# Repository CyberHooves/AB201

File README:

Haos Redro
==========

README for AB201
----------------

The AB201 is a class-AB audio amplifier module designed to have a sufficiently low profile to fit into 1U rack-mounting cases. It has been designed to provide up to 200W RMS output power before clipping. Output powers of up to 300W may be possible with sufficient cooling but is NOT reccommended with the specified heatsink (Fischer Electronic SK499 profile)

Notes on cooling:
-----------------
This module requires forced air cooling. The enclosure into which this module is installed must be designed to move air through the heatsink. There is provision for a two-lead temperature sensor for fan control and a TO-220 packaged NC thermostat to disconnect the output in case of overheating.

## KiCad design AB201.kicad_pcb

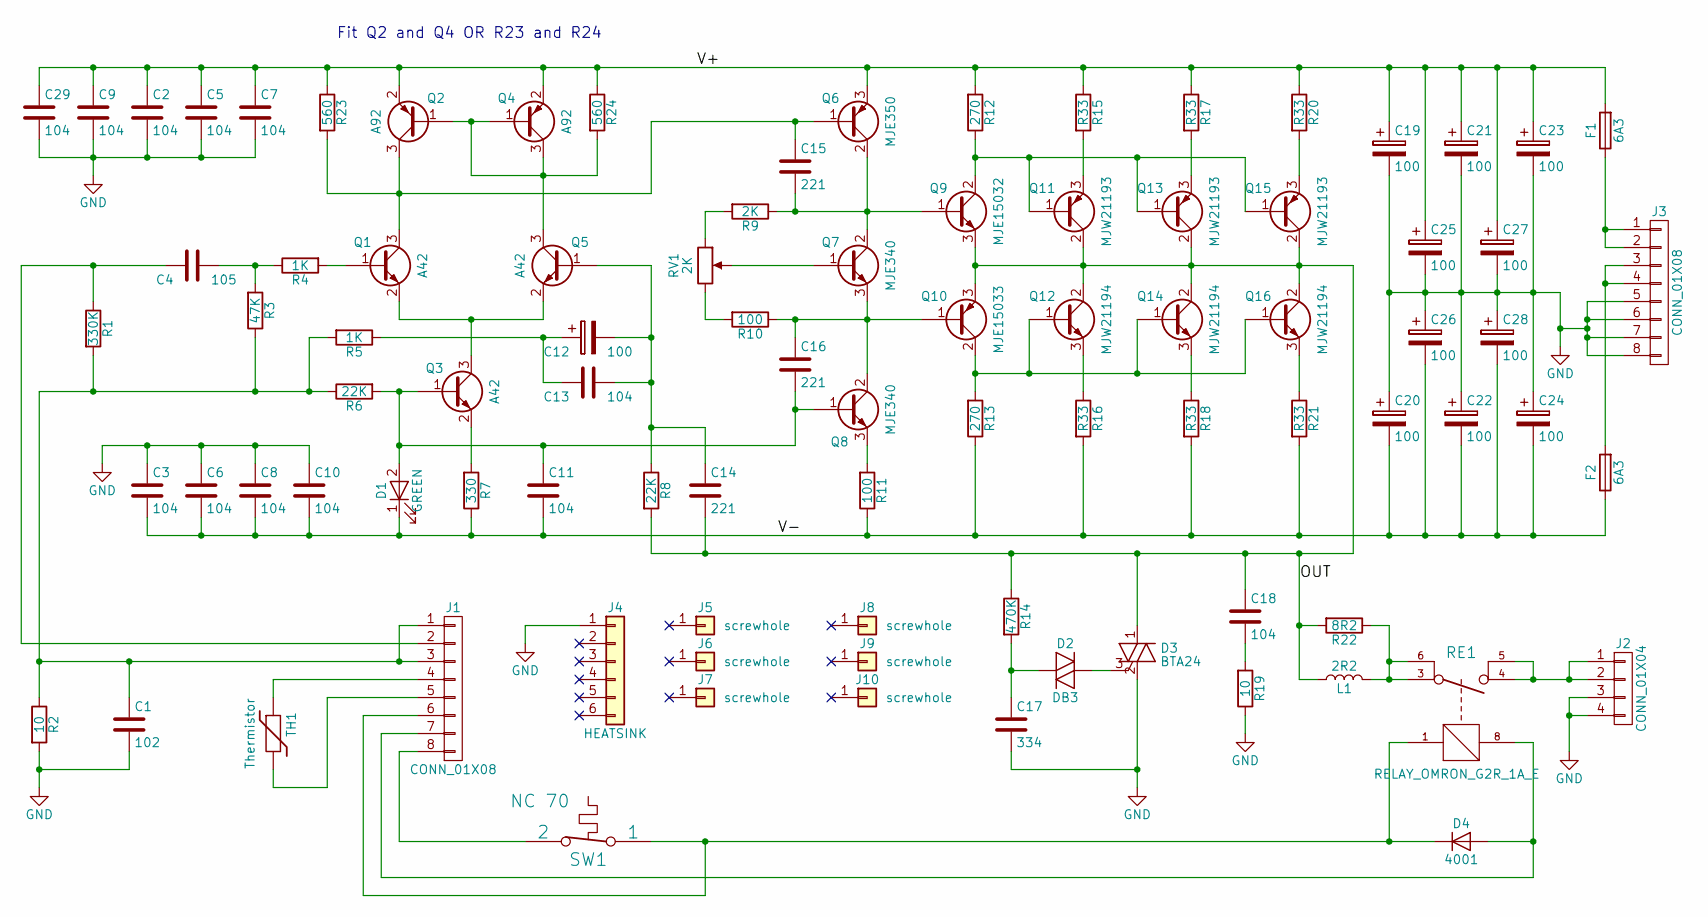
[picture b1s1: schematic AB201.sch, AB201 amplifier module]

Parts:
C1: 102; C_0805
C2, C3, C5, C6, C7, C8, C9, C10, C11, C29: 104; C_0805
C4: 105; C_Rect_L7.2mm_W5.5mm_P5.00mm_FKS2_FKP2_MKS2_MKP2
C12: 100; CP_Radial_D6.3mm_P2.50mm
C13: 104; C_Rect_L7.2mm_W3.0mm_P5.00mm_FKS2_FKP2_MKS2_MKP2
C14, C15, C16: 221; C_0805
C17: 334; C_0805
C18: 104; C_Rect_L7.2mm_W5.5mm_P5.00mm_FKS2_FKP2_MKS2_MKP2
C19, C20, C21, C22, C23, C24, C25, C26, C27, C28: 100; CP_Radial_D10.0mm_P5.00mm
D1: GREEN; LED_0805
D2: DB3; D_MiniMELF
D3: BTA24; TO-220-3_Vertical
D4: 4001; D_SMA
F1, F2: 6A3; Fuseholder5x20_horiz_open_universal_Type-III
J1: CONN_01X08; Pin_Header_Straight_2x04_Pitch2.54mm
J2: CONN_01X04; Molex_MiniFit-JR-5556-04A_2x02x4.20mm_Straight
J3: CONN_01X08; Molex_MiniFit-JR-5556-08A_2x04x4.20mm_Straight
J4: HEATSINK; HS-FISCHER-SK499-200-6A
J5, J6, J7, J8, J9, J10: screwhole; MH-H3.2-P7
L1: 2R2; Choke_SMD_10.4x10.4_H4.8
Q1, Q3, Q5: A42; SOT-23
Q2, Q4: A92; SOT-23
Q6: MJE350; TO-126_Vertical
Q7, Q8: MJE340; TO-126_Vertical
Q9: MJE15032; TO-220-3_Vertical
Q10: MJE15033; TO-220-3_Vertical
Q11, Q13, Q15: MJW21193; TO-247_TO-3P_Vertical
Q12, Q14, Q16: MJW21194; TO-247_TO-3P_Vertical
R1: 330K; R_0805
R2: 10; R_0805
R3: 47K; R_0805
R4, R5: 1K; R_0805
R6, R8: 22K; R_0805
R7: 330; R_0805
R9: 2K; R_0805
R10, R11: 100; R_0805
R12, R13: 270; R_1218
R14: 470K; R_0805
R15, R16, R17, R18, R20, R21: R33; R_Radial_Power_L13.0mm_W9.0mm_P5.00mm
R19: 10; R_Axial_DIN0922_L20.0mm_D9.0mm_P7.62mm_Vertical
R22: 8R2; R_Axial_Power_L20.0mm_W6.4mm_P7.62mm_Vertical
R23, R24: 560; R_0805
RE1: RELAY_OMRON_G2R_1A_E; RELAY-OMRON-G2R-1A-E
RV1: 2K; Potentiometer_Trimmer_Bourns_3296W
SW1: NC 70; TO-220-2_Vertical
TH1: Thermistor; PINHEAD1-2

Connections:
/OUT: C14.2, C18.1, D3.1 (A1), L1.1, Q9.3 (E), Q10.3 (E), Q11.2 (C), Q12.2 (C), Q13.2 (C), Q14.2 (C), Q15.2 (C), Q16.2 (C), R8.2, R14.1, R22.2
/V+: C2.1, C5.1, C7.1, C9.1, C19.1, C21.1, C23.1, C25.1, C27.1, C29.1, F1.2, Q2.2 (E), Q4.2 (E), Q6.3 (E), R12.2, R15.1, R17.1, R20.1, R23.1, R24.1
/V-: C3.2, C6.2, C8.2, C10.2, C11.2, C20.2, C22.2, C24.2, C26.2, C28.2, D1.1 (K), F2.1, R7.1, R11.1, R13.1, R16.2, R18.2, R21.2
GND: C1.2, C2.2, C3.1, C5.2, C6.1, C7.2, C8.1, C9.2, C10.1, C17.2, C19.2, C20.1, C21.2, C22.1, C23.2, C24.1, C25.2, C26.1, C27.2, C28.1, C29.2, D3.2 (A2), J2.3, J2.4, J3.5, J3.6, J3.7, J3.8, J4.1, R2.2, R19.1
unnamed: C1.1, J1.1, J1.3, R1.2, R2.1, R3.1, R5.2, R6.1
unnamed: C4.1, J1.2, R1.1
unnamed: C4.2, R3.2, R4.1
unnamed: C11.1, C16.2, D1.2 (A), Q3.1 (B), Q8.1 (B), R6.2
unnamed: C12.1, C13.1, R5.1
unnamed: C12.2, C13.2, C14.1, Q5.1 (B), R8.1
unnamed: C15.1, Q1.3 (C), Q2.3 (C), Q6.1 (B), R23.2
unnamed: C15.2, Q6.2 (C), Q7.2 (C), Q9.1 (B), R9.1
unnamed: C16.1, Q7.3 (E), Q8.2 (C), Q10.1 (B), R10.1
unnamed: C17.1, D2.1 (K), R14.2
unnamed: C18.2, R19.2
unnamed: D2.2 (A), D3.3 (G)
unnamed: D4.1 (K), J1.6, RE1.1 (C1), SW1.1
unnamed: D4.2 (A), J1.7, RE1.8 (C2)
unnamed: F1.1, J3.1, J3.2
unnamed: F2.2, J3.3, J3.4
unnamed: J1.4, TH1.1
unnamed: J1.5, TH1.2
unnamed: J1.8, SW1.2
unnamed: J2.1, J2.2, RE1.4, RE1.5
unnamed: L1.2, R22.1, RE1.3, RE1.6
unnamed: Q1.1 (B), R4.2
unnamed: Q1.2 (E), Q3.3 (C), Q5.2 (E)
unnamed: Q2.1 (B), Q4.1 (B), Q4.3 (C), Q5.3 (C), R24.2
unnamed: Q3.2 (E), R7.2
unnamed: Q7.1 (B), RV1.2
unnamed: Q8.3 (E), R11.2
unnamed: Q10.2 (C), Q12.1 (B), Q14.1 (B), Q16.1 (B), R13.2
unnamed: Q9.2 (C), Q11.1 (B), Q13.1 (B), Q15.1 (B), R12.1
unnamed: Q11.3 (E), R15.2
unnamed: Q12.3 (E), R16.1
unnamed: Q13.3 (E), R17.2
unnamed: Q14.3 (E), R18.1
unnamed: Q15.3 (E), R20.2
unnamed: Q16.3 (E), R21.1
unnamed: R9.2, RV1.1
unnamed: R10.2, RV1.3

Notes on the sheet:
Fit Q2 and Q4 OR R23 and R24

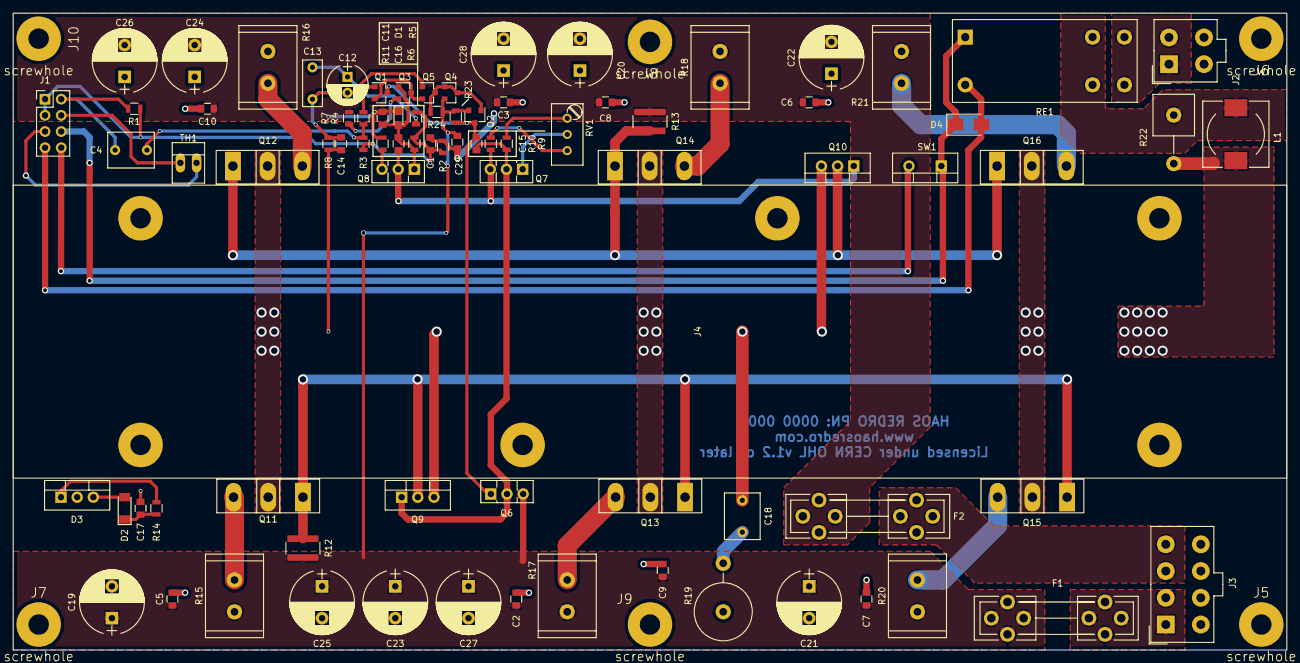
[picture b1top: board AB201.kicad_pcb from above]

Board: 2 copper layers, 200.0 x 100.0 mm, 90 parts (0 on the bottom side), 41 nets.

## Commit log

2018-04-16 PCB layout updated
2019-02-20 PCB changes

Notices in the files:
AB201.kicad_pcb:
Copyright Taiyo Rawle 2018
Licensed under CERN OHL v.1.2 or later
